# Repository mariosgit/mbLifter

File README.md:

# mb'Lifter 

## What is it

It's a amplifier and attenuator, both coupled and controlled by one knob.

Input -> Amplify -> Attenuate -> Output

or

Input -> Attenuate -> Amplify -> Output.

the middle connection (gained or attenuated signal) can be routed anywhere.

Gain range: -18...+18 dB

It has 2 channels doing this.

Clip indicator - lights up when one of the channels opamps runs into clipping, that is signal level above +-10V peak to peak.

Other features Reverse voltage protection, requires +-12V and needs +-25mA. Width = 5HP = 25mm = almost 1".

### But Why ?

Original idea was to drive an overdrive/distortion unit, so it gains the signal, passes it to the distortion stuff, and then it attenuates to the original levels. In this way the distorted signal does not get louder only distorteder.

### Usecases

* Drive signal into distortion.

### Misuseable as

* InOut - Input an Aux signal (gain Line level to Rack level) AND Output Rack signals with Line level.
* Effect Adapter - Use Guitar effects in your rack - Attenuate to FX(line) level -> FX -> Gain back into Rack Level. Or other way around - use your rack as guitar FX unit.
* Instrument interface - cascade both channels to achive max gain of 36dB, sufficient for Mics and Guitars.
* ...

## Files in repo...

### /pcb

* Lifter01 is the beta version, left here as reference. Had a view minor bugs.
  * Missing feedback caps.
  * 2 wrongly flipped opamp gates.
* Lifter02 - current production version, labeled as "version1.0"
* FrontPCB - as name says.

## License

#### Attribution-NonCommercial-ShareAlike - CC BY-NC-SA 

```
Attribution — You must give appropriate credit, provide a link to the license, and indicate if changes were made. You may do so in any reasonable manner, but not in any way that suggests the licensor endorses you or your use.

NonCommercial — You may not use the material for commercial purposes.

ShareAlike — If you remix, transform, or build upon the material, you must distribute your contributions under the same license as the original.

No additional restrictions — You may not apply legal terms or technological measures that legally restrict others from doing anything the license permits.
```
[All the legal blabla here](https://creativecommons.org/licenses/by-nc-sa/4.0/legalcode)

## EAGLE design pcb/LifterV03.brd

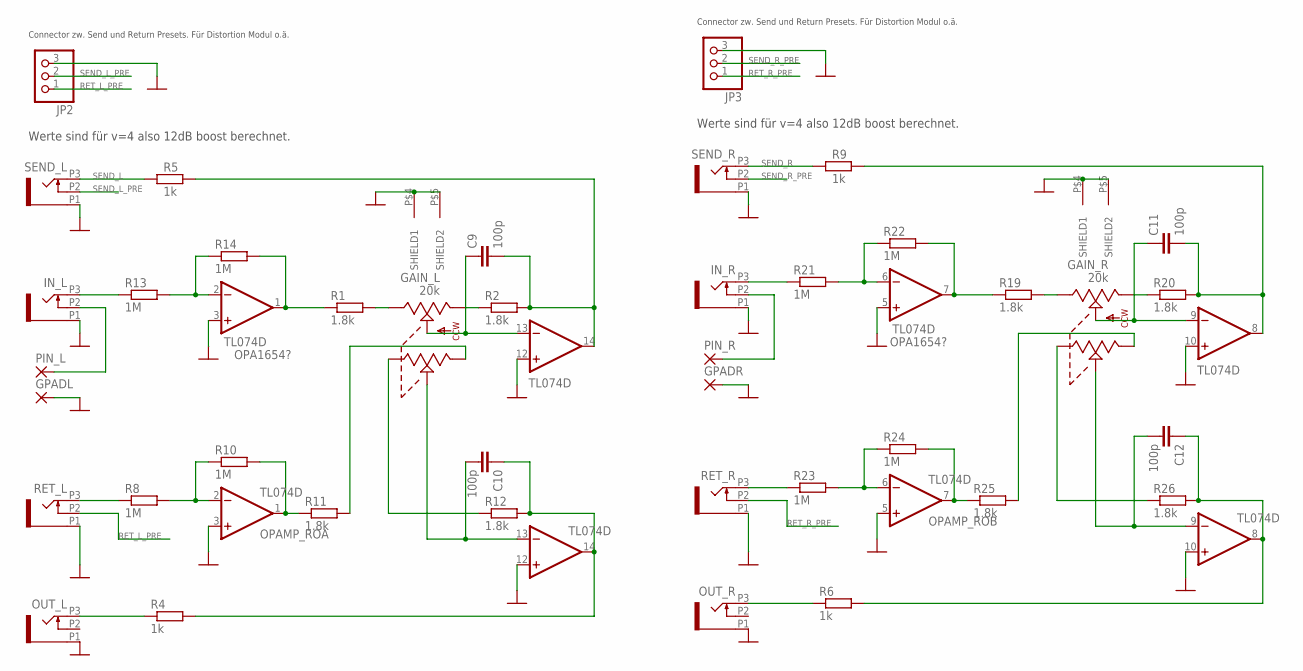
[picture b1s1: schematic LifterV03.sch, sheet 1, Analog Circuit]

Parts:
C9, C10, C11, C12: 100p; C0603
GAIN_L: 20k; TT_2TAP_VERTICAL
GAIN_R: 20k; TT_2TAP_VERTICAL
GPADL: 3,17/1,3
GPADR: 3,17/1,3
IN_L: PJ301_THONKICONN6; WQP_PJ_301M6
IN_R: PJ301_THONKICONN6; WQP_PJ_301M6
JP2, JP3: PINHD-1X3; 1X03
OPAMP_IS: TL074D; SO14
OPAMP_RO: TL074D; SO14
OUT_L: PJ301_THONKICONN6; WQP_PJ_301M6
OUT_R: PJ301_THONKICONN6; WQP_PJ_301M6
PIN_L: 3,17/1,3
PIN_R: 3,17/1,3
R1, R2, R11, R12, R19, R20, R25, R26: 1.8k; R0603
R4, R5, R6, R9: 1k; R0603
R8, R10, R13, R14, R21, R22, R23, R24: 1M; R0603
RET_L: PJ301_THONKICONN6; WQP_PJ_301M6
RET_R: PJ301_THONKICONN6; WQP_PJ_301M6
SEND_L: PJ301_THONKICONN6; WQP_PJ_301M6
SEND_R: PJ301_THONKICONN6; WQP_PJ_301M6

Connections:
GND: GAIN_L.P$4 (SHIELD1), GAIN_L.P$5 (SHIELD2), GAIN_R.P$4 (SHIELD1), GAIN_R.P$5 (SHIELD2), GPADL.1, GPADR.1, IN_L.P1 (1), IN_R.P1 (1), JP2.3, JP3.3, OPAMP_IS.3 (+IN), OPAMP_IS.5 (+IN), OPAMP_IS.10 (+IN), OPAMP_IS.12 (+IN), OPAMP_RO.3 (+IN), OPAMP_RO.5 (+IN), OPAMP_RO.10 (+IN), OPAMP_RO.12 (+IN), OUT_L.P1 (1), OUT_R.P1 (1), RET_L.P1 (1), RET_R.P1 (1), SEND_L.P1 (1), SEND_R.P1 (1); also elsewhere on the board
unnamed: GAIN_L.CCW, R2.1
unnamed: GAIN_L.CW, R1.2
unnamed: C9.2, OPAMP_IS.14 (OUT), R2.2, R5.2
unnamed: C9.1, GAIN_L.CENTER, OPAMP_IS.13 (-IN)
unnamed: IN_L.P3 (3), R13.1
unnamed: OPAMP_IS.2 (-IN), R13.2, R14.1
unnamed: OPAMP_IS.1 (OUT), R1.1, R14.2
unnamed: OUT_L.P3 (3), R4.1
unnamed: R8.1, RET_L.P3 (3)
unnamed: IN_L.P2 (2), PIN_L.1
unnamed: OPAMP_RO.2 (-IN), R8.2, R10.1
unnamed: GAIN_L.CW1, R12.1
unnamed: OPAMP_RO.1 (OUT), R10.2, R11.1
unnamed: GAIN_L.CCW1, R11.2
unnamed: C10.2, GAIN_L.CENTER1, OPAMP_RO.13 (-IN)
unnamed: C10.1, OPAMP_RO.14 (OUT), R4.2, R12.2
unnamed: IN_R.P2 (2), PIN_R.1
unnamed: GAIN_R.CW, R19.2
unnamed: C11.1, GAIN_R.CENTER, OPAMP_IS.9 (-IN)
unnamed: GAIN_R.CCW, R20.1
unnamed: IN_R.P3 (3), R21.1
unnamed: OPAMP_IS.6 (-IN), R21.2, R22.1
unnamed: OPAMP_IS.7 (OUT), R19.1, R22.2
unnamed: R23.1, RET_R.P3 (3)
unnamed: OPAMP_RO.6 (-IN), R23.2, R24.1
unnamed: OPAMP_RO.7 (OUT), R24.2, R25.1
unnamed: GAIN_R.CCW1, R25.2
unnamed: GAIN_R.CW1, R26.1
unnamed: C12.2, GAIN_R.CENTER1, OPAMP_RO.9 (-IN)
unnamed: C11.2, OPAMP_IS.8 (OUT), R9.2, R20.2
unnamed: OUT_R.P3 (3), R6.1
unnamed: C12.1, OPAMP_RO.8 (OUT), R6.2, R26.2
RET_L_PRE: JP2.1, RET_L.P2 (2)
RET_R_PRE: JP3.1, RET_R.P2 (2)
SEND_L: R5.1, SEND_L.P3 (3); also elsewhere on the board
SEND_L_PRE: JP2.2, SEND_L.P2 (2)
SEND_R: R9.1, SEND_R.P3 (3); also elsewhere on the board
SEND_R_PRE: JP3.2, SEND_R.P2 (2)

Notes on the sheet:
OPA1654?
Connector zw. Send und Return Presets. Für Distortion Modul o.ä.
Werte sind für v=4 also 12dB boost berechnet.

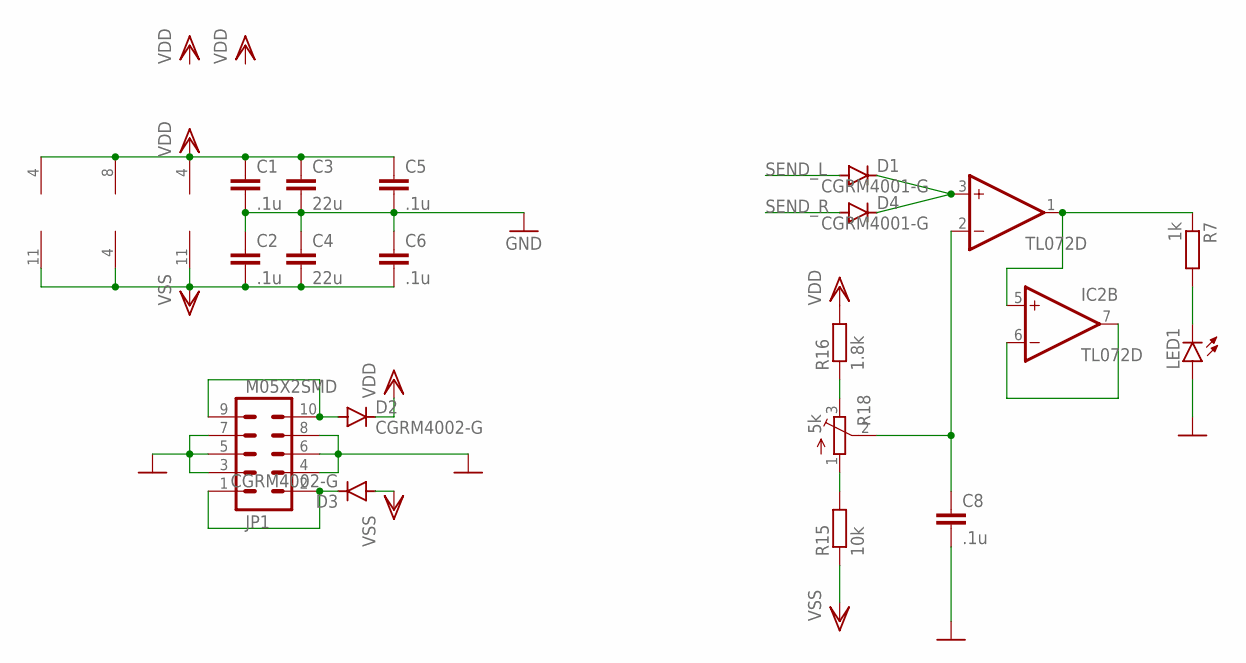
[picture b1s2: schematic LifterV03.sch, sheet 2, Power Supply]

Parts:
C1, C2, C5, C6, C8: .1u; C0603
C3, C4: 22u; C1210
D1, D4: CGRM4001-G; SOD-123_MINI-SMA
D2, D3: CGRM4002-G; SOD-123_MINI-SMA
IC2: TL072D; SO08
JP1: M05X2SMD; 2X5-SMD
LED1: LED3MM
OPAMP_IS: TL074D; SO14
OPAMP_RO: TL074D; SO14
R7: 1k; R0603
R15: 10k; R0603
R16: 1.8k; R0603
R18: 5k; 3223G; MOUSER 652-TC33X-2-502G

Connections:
GND: C1.2, C2.1, C3.2, C4.1, C5.2, C6.1, C8.2, JP1.3, JP1.4, JP1.5, JP1.6, JP1.7, JP1.8, LED1.A; also elsewhere on the board
unnamed: IC2.6 (-IN), IC2.7 (OUT)
unnamed: D2.A, JP1.9, JP1.10
unnamed: D1.C, D4.C, IC2.3 (+IN)
unnamed: D3.C, JP1.1, JP1.2
unnamed: LED1.K (C), R7.2
unnamed: IC2.1 (OUT), IC2.5 (+IN), R7.1
unnamed: C8.1, IC2.2 (-IN), R18.2 (S)
unnamed: R16.1, R18.3 (E)
unnamed: R15.2, R18.1 (A)
SEND_L: D1.A; also elsewhere on the board
SEND_R: D4.A; also elsewhere on the board
VDD: C1.1, C3.1, C5.1, D2.C, IC2.8 (V+), OPAMP_IS.4 (V+), OPAMP_RO.4 (V+), R16.2
VSS: C2.2, C4.2, C6.2, D3.A, IC2.4 (V-), OPAMP_IS.11 (V-), OPAMP_RO.11 (V-), R15.1

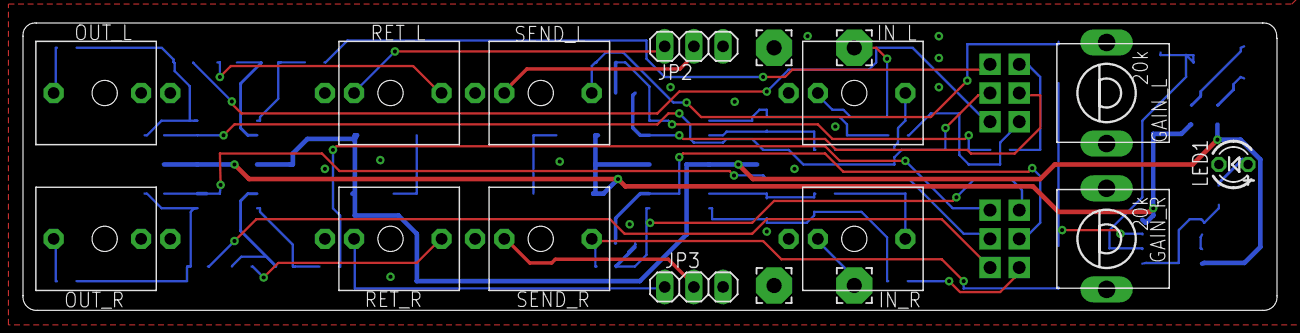
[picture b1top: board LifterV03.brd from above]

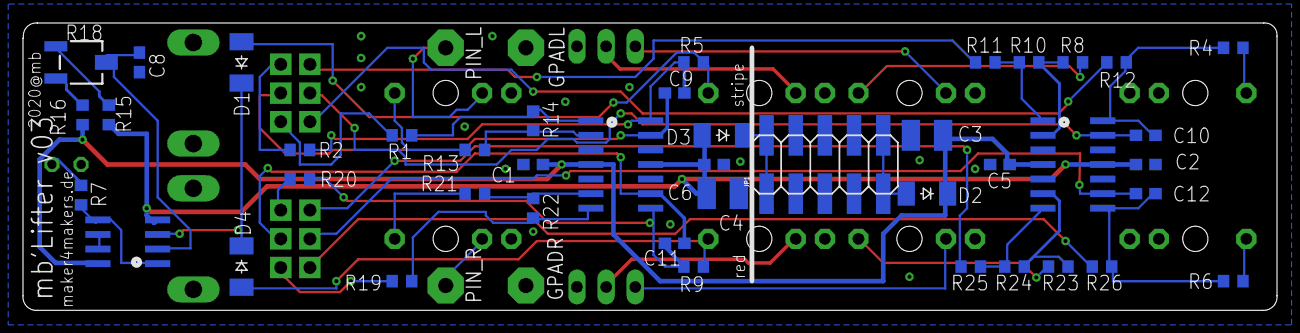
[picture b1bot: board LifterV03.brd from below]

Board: 2 copper layers, 109.2 x 25.0 mm, 60 parts (43 on the bottom side), 50 nets.

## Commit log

2020-04-05 added images
2020-04-05 more detail
2020-04-05 more images
2020-04-05 mhm?
2020-04-28 increased pot drill 9mm/355mil
2020-04-29 Minor changes to pcb text, Added Spacer and Isolator, Added License
2021-06-02 added a simulation file
2021-06-02 added diode distortion sim
2021-07-12 BigMac changes.
